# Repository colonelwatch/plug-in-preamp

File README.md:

# plug-in-preamp

## License

PCB design files are licensed under the CERN Open Hardware Licence Version 2 - Permissive. See the `LICENSE` file for details.

### SnapMagic assets

The symbols, footprints, and 3D models for the following components were downloaded from SnapMagic.

- `SP-3541` (authored by Same Sky)
- `SJ3-35063BG` (authored by Same Sky)

These files were acquired under the [Creative Commons Attribution-ShareAlike 4.0 (CC BY-SA 4.0)](https://creativecommons.org/licenses/by-sa/4.0/) license with the [Design Exception 1.0](https://support.snapmagic.com/en/articles/2957815-what-is-the-design-exception-1-0), provided for reference below:

> You have permission to propagate a work of a design, design file(s), and/or manufactured board(s) formed by combining CAD symbols, footprints, and 3D models provided by SnapMagic, even if such propagation would otherwise violate the terms of CC BY-SA. You may then convey such a combination under terms of your choice.

For more information about SnapMagic distribution, see the [FAQ page on SnapMagic](https://support.snapmagic.com/en/articles/2957814-what-is-the-license-for-symbols-and-footprints).

The aforementioned SnapMagic files are distributed here unmodified and remain licensed under CC BY-SA 4.0 with the Design Exception 1.0. However, in accordance with the Design Exception, the combined PCB design that utilizes them is licensed under the CERN Open Hardware Licence Version 2 - Permissive.

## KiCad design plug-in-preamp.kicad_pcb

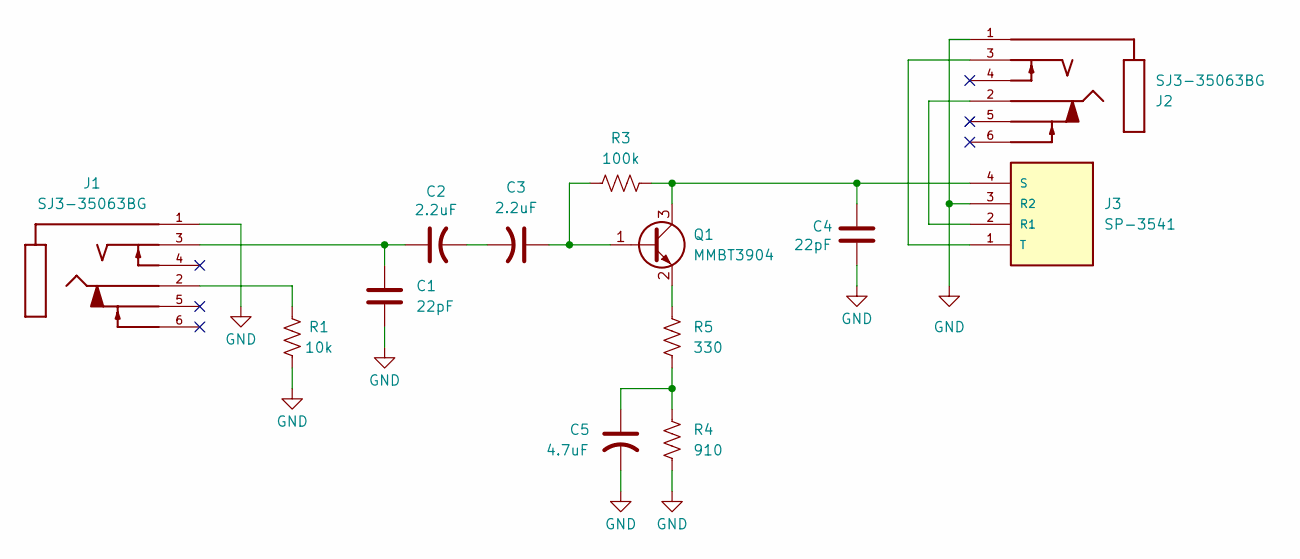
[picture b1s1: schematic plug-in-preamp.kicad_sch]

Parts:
C1, C4: 22pF; C_0603_1608Metric
C2, C3: 2.2uF; C_0603_1608Metric
C5: 4.7uF; C_1206_3216Metric
J1, J2: SJ3-35063BG; SAMESKY_SJ3-35063BG; PARTREV 1.0
J3: SP-3541; CUI_SP-3541; PART_REV 1.0
Q1: MMBT3904; SOT-23
R1: 10k; R_0805_2012Metric
R3: 100k; R_0805_2012Metric
R4: 910; R_0805_2012Metric
R5: 330; R_0805_2012Metric

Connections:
GND: C1.2, C4.2, C5.2, J1.1, J2.1, J3.3 (R2), R1.1, R4.2
unnamed: C1.1, C2.1, J1.3
unnamed: C2.2, C3.2
unnamed: C5.1, R4.1, R5.2
unnamed: J1.2, R1.2
unnamed: J2.2, J3.2 (R1)
unnamed: C4.1, J3.4 (S), Q1.3 (C), R3.1
unnamed: J2.3, J3.1 (T)
unnamed: C3.1, Q1.1 (B), R3.2
unnamed: Q1.2 (E), R5.1

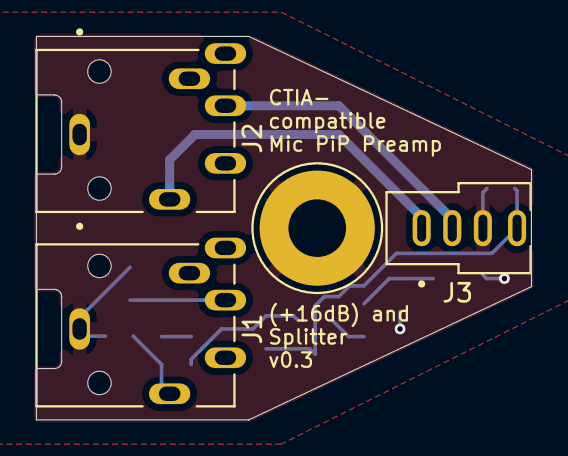
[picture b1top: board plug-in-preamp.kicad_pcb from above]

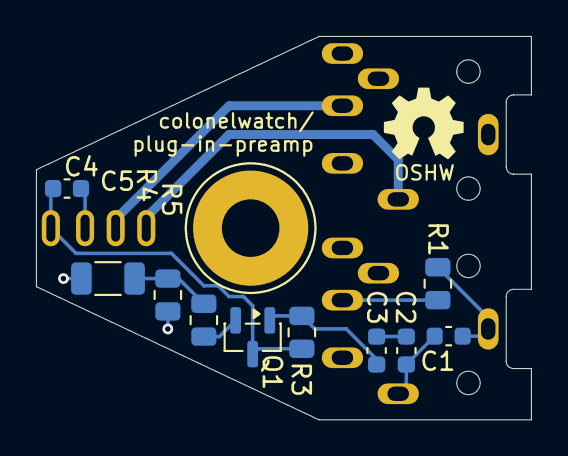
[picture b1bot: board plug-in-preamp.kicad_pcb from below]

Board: 2 copper layers, 27.5 x 21.3 mm, 13 parts (10 on the bottom side), 10 nets.
